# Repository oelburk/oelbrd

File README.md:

<!-- PROJECT SHIELDS -->
[![Contributors][contributors-shield]][contributors-url]
[![Forks][forks-shield]][forks-url]
[![Stargazers][stars-shield]][stars-url]
[![Issues][issues-shield]][issues-url]
[![MIT License][license-shield]][license-url]

<!-- PROJECT LOGO -->
<br />
<div align="center">

<h3 align="center">OELBRD</h3>

  <p align="center">
    Custom designed keyboard PCB and Firmware
    <br />
    <a href="https://github.com/oelburk/oelbrd/issues">Report Bug</a>
    ·
    <a href="https://github.com/oelburk/oelbrd/issues">Request Feature</a>
  </p>
</div>

<!-- TABLE OF CONTENTS -->
<details>
  <summary>Table of Contents</summary>
  <ol>
    <li>
      <a href="#about-the-project">About The Project</a>
      <ul>
        <li><a href="#built-with">Built With</a></li>
      </ul>
    </li>
    <li>
      <a href="#getting-started">Getting Started (Keymap setup)</a>
      <ul>
        <li><a href="#prerequisites">Prerequisites</a></li>
        <li><a href="#installation">Creating a keymap</a></li>
      </ul>
    </li>
    <li><a href="#contributing">Contributing</a></li>
    <li><a href="#license">License</a></li>
    <li><a href="#acknowledgments">Acknowledgments</a></li>
  </ol>
</details>

<!-- ABOUT THE PROJECT -->
## About The Project

![Product Name Screen Shot][product-screenshot]

Small project containing the PCB design files (KiCad project) along with the source code for different keymaps for my custom designed 60% keyboard.

<p align="right">(<a href="#readme-top">back to top</a>)</p>

### Built With

* [KiCad](https://www.kicad.org/download/windows/)
  * https://github.com/egladman/keebs.pretty
  * https://github.com/tmk/keyboard_parts.pretty
* [QMK](https://qmk.fm/)

<p align="right">(<a href="#readme-top">back to top</a>)</p>

<!-- GETTING STARTED -->
## Getting Started (Keymap setup)

This is an example of how you can create your own keymap for the oelbrd.

### Prerequisites
* Text editor of choice
* [QMK](https://github.com/qmk/qmk_firmware/blob/master/docs/newbs.md)

### Creating a keymap

1. Clone the repo
   ```sh
   git clone https://github.com/oelburk/oelbrd.git
   ```
2. Create new folder in keymaps folder
   ```sh
   mkdir QMK/keymaps/my-keymap
   ```
3. Copy default keymap (optional)
   ```sh
   cp QMK/keymaps/default/keymap.c QMK/keymaps/my-keymap
   ```
4. Edit `keymap.c` with preferred layout
5. Create oelbrd in QMK
   ```sh
   qmk new-keyboard oelbrd
   ```
6. Copy over contents from the QMK folder to new oelbrd directory in QMK repo, usally `../qmk_firmware/keyboards/oelbrd`
7. Compile the new keymap using QMK
   ```sh
   qmk compile -kb oelbrd -kb my-keymap
   ```
8. Flash new layout

### VIA support

There are currently some strange issues with the implemented VIA support, complaining about missing version definitons etc.

To fix this issue:
1. Open `qmk_firware/quantum/via.h`
2. Replace the define `VIA_PROTOCOL_VERSION` at row 62
   ```C
    VIA_PROTOCOL_VERSION 0x0009
   ```
3. Re-compile your keymap.
4. Enjoy VIA!

<p align="right">(<a href="#readme-top">back to top</a>)</p>

<!-- CONTRIBUTING -->
## Contributing

Contributions are what make the open source community such an amazing place to learn, inspire, and create. Any contributions you make are **greatly appreciated**.

If you have a suggestion that would make this better, please fork the repo and create a pull request. You can also simply open an issue with the tag "enhancement".
Don't forget to give the project a star! Thanks again!

1. Fork the Project
2. Create your Feature Branch (`git checkout -b feature/AmazingFeature`)
3. Commit your Changes (`git commit -m 'Add some AmazingFeature'`)
4. Push to the Branch (`git push origin feature/AmazingFeature`)
5. Open a Pull Request

<p align="right">(<a href="#readme-top">back to top</a>)</p>

<!-- LICENSE -->
## License

Distributed under the MIT License. See `LICENSE.txt` for more information.

<p align="right">(<a href="#readme-top">back to top</a>)</p>

<!-- ACKNOWLEDGMENTS -->
## Acknowledgments

* [Shoutout othneildrew for nice README template](https://github.com/othneildrew/Best-README-Template)
* [Swe Mech Keebs Community](http://mekaniskatangentbord.se/)

<p align="right">(<a href="#readme-top">back to top</a>)</p>

<!-- MARKDOWN LINKS & IMAGES -->
<!-- https://www.markdownguide.org/basic-syntax/#reference-style-links -->
[contributors-shield]: https://img.shields.io/github/contributors/oelburk/oelbrd.svg?style=for-the-badge
[contributors-url]: https://github.com/oelburk/oelbrd/graphs/contributors
[forks-shield]: https://img.shields.io/github/forks/oelburk/oelbrd.svg?style=for-the-badge
[forks-url]: https://github.com/oelburk/oelbrd/network/members
[stars-shield]: https://img.shields.io/github/stars/oelburk/oelbrd.svg?style=for-the-badge
[stars-url]: https://github.com/oelburk/oelbrd/stargazers
[issues-shield]: https://img.shields.io/github/issues/oelburk/oelbrd.svg?style=for-the-badge
[issues-url]: https://github.com/oelburk/oelbrd/issues
[license-shield]: https://img.shields.io/github/license/oelburk/oelbrd.svg?style=for-the-badge
[license-url]: https://github.com/oelburk/oelbrd/blob/master/LICENSE.txt
[linkedin-shield]: https://img.shields.io/badge/-LinkedIn-black.svg?style=for-the-badge&logo=linkedin&colorB=555
[linkedin-url]: https://linkedin.com/in/linkedin_username
[product-screenshot]: Design/oelbrd-mk1.jpg
[Next.js]: https://img.shields.io/badge/next.js-000000?style=for-the-badge&logo=nextdotjs&logoColor=white
[Next-url]: https://nextjs.org/
[React.js]: https://img.shields.io/badge/React-20232A?style=for-the-badge&logo=react&logoColor=61DAFB
[React-url]: https://reactjs.org/
[Vue.js]: https://img.shields.io/badge/Vue.js-35495E?style=for-the-badge&logo=vuedotjs&logoColor=4FC08D
[Vue-url]: https://vuejs.org/
[Angular.io]: https://img.shields.io/badge/Angular-DD0031?style=for-the-badge&logo=angular&logoColor=white
[Angular-url]: https://angular.io/
[Svelte.dev]: https://img.shields.io/badge/Svelte-4A4A55?style=for-the-badge&logo=svelte&logoColor=FF3E00
[Svelte-url]: https://svelte.dev/
[Laravel.com]: https://img.shields.io/badge/Laravel-FF2D20?style=for-the-badge&logo=laravel&logoColor=white
[Laravel-url]: https://laravel.com
[Bootstrap.com]: https://img.shields.io/badge/Bootstrap-563D7C?style=for-the-badge&logo=bootstrap&logoColor=white
[Bootstrap-url]: https://getbootstrap.com
[JQuery.com]: https://img.shields.io/badge/jQuery-0769AD?style=for-the-badge&logo=jquery&logoColor=white
[JQuery-url]: https://jquery.com

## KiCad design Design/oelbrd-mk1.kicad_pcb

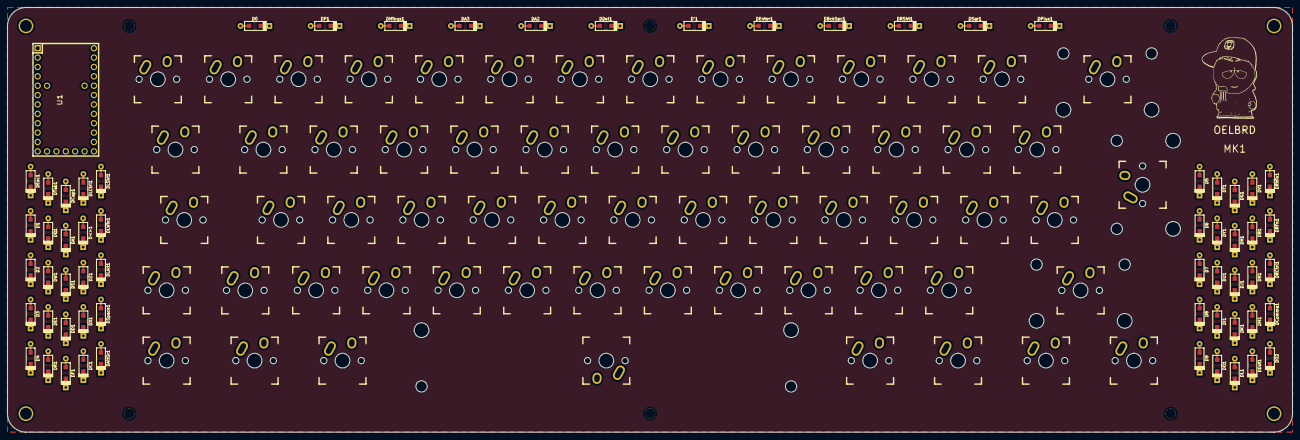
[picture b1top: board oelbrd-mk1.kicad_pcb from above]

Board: 2 copper layers, 348.0 x 115.0 mm, 135 parts (0 on the bottom side), 82 nets, no tracks yet.

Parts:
D0, D1, D2, D3, D4, D5, D6, D7, D8, D9: D; D_SOD123_axial
D'1: D; D_SOD123_axial
D<>1: D; D_SOD123_axial
DA1, DA2, DA3: D; D_SOD123_axial
DAltGr1: D; D_SOD123_axial
DB1: D; D_SOD123_axial
DBckSpc1: D; D_SOD123_axial
DC1: D; D_SOD123_axial
DCap1: D; D_SOD123_axial
DComma1: D; D_SOD123_axial
DD1: D; D_SOD123_axial
DDel1: D; D_SOD123_axial
DDot1: D; D_SOD123_axial
DE1: D; D_SOD123_axial
DEnter1: D; D_SOD123_axial
DEsc1: D; D_SOD123_axial
DF1: D; D_SOD123_axial
DG1: D; D_SOD123_axial
DH1: D; D_SOD123_axial
DI1: D; D_SOD123_axial
DJ1: D; D_SOD123_axial
DK1: D; D_SOD123_axial
DL1: D; D_SOD123_axial
DLAlt1: D; D_SOD123_axial
DLCtrl1: D; D_SOD123_axial
DLSht1: D; D_SOD123_axial
DLWin1: D; D_SOD123_axial
DM1: D; D_SOD123_axial
DMinus1: D; D_SOD123_axial
DN1: D; D_SOD123_axial
DO1, DO2: D; D_SOD123_axial
DP1: D; D_SOD123_axial
DPlus1: D; D_SOD123_axial
DQ1: D; D_SOD123_axial
DR1: D; D_SOD123_axial
DRCtrl1: D; D_SOD123_axial
DRFn1: D; D_SOD123_axial
DRSht1: D; D_SOD123_axial
DRWin1: D; D_SOD123_axial
DS1: D; D_SOD123_axial
DSpace1: D; D_SOD123_axial
DSqr1: D; D_SOD123_axial
DT1: D; D_SOD123_axial
DTab1: D; D_SOD123_axial
DU1: D; D_SOD123_axial
DV1: D; D_SOD123_axial
DW1: D; D_SOD123_axial
DX1: D; D_SOD123_axial
DY1: D; D_SOD123_axial
DZ1: D; D_SOD123_axial
HOLE_M2.6, HOLE_M2.6#2, HOLE_M2.6#3, HOLE_M2.6#4, HOLE_M2.6#5, HOLE_M2.6#6: VAL**; HOLE_M2.6
HOLE_M3, HOLE_M3#2, HOLE_M3#3, HOLE_M3#4: VAL**; HOLE_M3
K0, K1, K2, K3, K4, K5, K6, K7, K8, K9: KEYSW; Mx_Alps_100
K'1: KEYSW; Mx_Alps_100
K<>1: KEYSW; Mx_Alps_100
KA1, KA2, KA3: KEYSW; Mx_Alps_100
KAltGr1: KEYSW; Mx_Alps_125
KB1: KEYSW; Mx_Alps_100
KBckSpc1: KEYSW; Mx_Alps_200
KC1: KEYSW; Mx_Alps_100
KCap1: KEYSW; Mx_Alps_175
KComma1: KEYSW; Mx_Alps_100
KD1: KEYSW; Mx_Alps_100
KDel1: KEYSW; Mx_Alps_100
KDot1: KEYSW; Mx_Alps_100
KE1: KEYSW; Mx_Alps_100
KEnter1: KEYSW; Mx_Alps_200
KEsc1: KEYSW; Mx_Alps_100
KF1: KEYSW; Mx_Alps_100
KG1: KEYSW; Mx_Alps_100
KH1: KEYSW; Mx_Alps_100
KI1: KEYSW; Mx_Alps_100
KJ1: KEYSW; Mx_Alps_100
KK1: KEYSW; Mx_Alps_100
KL1: KEYSW; Mx_Alps_100
KLAlt1: KEYSW; Mx_Alps_125
KLCtrl1: KEYSW; Mx_Alps_125
KLSht1: KEYSW; Mx_Alps_125
KLWin1: KEYSW; Mx_Alps_125
KM1: KEYSW; Mx_Alps_100
KMinus1: KEYSW; Mx_Alps_100
KN1: KEYSW; Mx_Alps_100
KO1, KO2: KEYSW; Mx_Alps_100
KP1: KEYSW; Mx_Alps_100
KPlus1: KEYSW; Mx_Alps_100
KQ1: KEYSW; Mx_Alps_100
KR1: KEYSW; Mx_Alps_100
KRCtrl1: KEYSW; Mx_Alps_125
KRFn1: KEYSW; Mx_Alps_125
KRSht1: KEYSW; Mx_Alps_275
KRWin1: KEYSW; Mx_Alps_125
KS1: KEYSW; Mx_Alps_100
KSpace1: KEYSW; Mx_Alps_625
KSqr1: KEYSW; Mx_Alps_100
KT1: KEYSW; Mx_Alps_100
KTab1: KEYSW; Mx_Alps_150
KU1: KEYSW; Mx_Alps_100
KV1: KEYSW; Mx_Alps_100
KW1: KEYSW; Mx_Alps_100
KX1: KEYSW; Mx_Alps_100
KY1: KEYSW; Mx_Alps_100
KZ1: KEYSW; Mx_Alps_100
U1: TEENSY2.0; Teensy_20

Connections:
/col0: KCap1.1, KEsc1.1, KLCtrl1.1, KLSht1.1, KTab1.1, U1.21
/col1: K1.1, K<>1.1, KA1.1, KLWin1.1, KQ1.1, U1.22
/col2: K2.1, KLAlt1.1, KS1.1, KW1.1, KZ1.1, U1.6
/col3: K3.1, KD1.1, KE1.1, KSpace1.1, KX1.1, U1.11
/col4: K4.1, KAltGr1.1, KC1.1, KF1.1, KR1.1, U1.12
/col5: K5.1, KG1.1, KRWin1.1, KT1.1, KV1.1, U1.7
/col6: K6.1, KB1.1, KH1.1, KRFn1.1, KY1.1, U1.8
/col7: K7.1, KJ1.1, KN1.1, KRCtrl1.1, KU1.1, U1.9
/col8: K8.1, KI1.1, KK1.1, KM1.1, U1.10
/col9: K9.1, KComma1.1, KL1.1, KO1.1, U1.17
/col10: K0.1, KDot1.1, KO2.1, KP1.1, U1.13
/col11: KA2.1, KA3.1, KMinus1.1, KPlus1.1, U1.19
/col12: K'1.1, KDel1.1, KRSht1.1, KSqr1.1, U1.31
/col13: KBckSpc1.1, KEnter1.1, U1.28
/row0: D0.1, D1.1, D2.1, D3.1, D4.1, D5.1, D6.1, D7.1, D8.1, D9.1, DBckSpc1.1, DDel1.1, DEsc1.1, DPlus1.1, U1.2
/row1: DA2.1, DE1.1, DEnter1.1, DI1.1, DO1.1, DP1.1, DQ1.1, DR1.1, DSqr1.1, DT1.1, DTab1.1, DU1.1, DW1.1, DY1.1, U1.3
/row2: D'1.1, DA1.1, DA3.1, DCap1.1, DD1.1, DF1.1, DG1.1, DH1.1, DJ1.1, DK1.1, DL1.1, DO2.1, DS1.1, U1.4
/row3: D<>1.1, DB1.1, DC1.1, DComma1.1, DDot1.1, DLSht1.1, DM1.1, DMinus1.1, DN1.1, DRSht1.1, DV1.1, DX1.1, DZ1.1, U1.5
/row4: DAltGr1.1, DLAlt1.1, DLCtrl1.1, DLWin1.1, DRCtrl1.1, DRFn1.1, DRWin1.1, DSpace1.1, U1.20
GND: U1.1, U1.15
unnamed: D0.2, K0.2
unnamed: D1.2, K1.2
unnamed: D2.2, K2.2
unnamed: D3.2, K3.2
unnamed: D4.2, K4.2
unnamed: D5.2, K5.2
unnamed: D6.2, K6.2
unnamed: D7.2, K7.2
unnamed: D8.2, K8.2
unnamed: D9.2, K9.2
unnamed: D'1.2, K'1.2
unnamed: D<>1.2, K<>1.2
unnamed: DA1.2, KA1.2
unnamed: DA2.2, KA2.2
unnamed: DA3.2, KA3.2
unnamed: DAltGr1.2, KAltGr1.2
unnamed: DB1.2, KB1.2
unnamed: DBckSpc1.2, KBckSpc1.2
unnamed: DC1.2, KC1.2
unnamed: DCap1.2, KCap1.2
unnamed: DComma1.2, KComma1.2
unnamed: DD1.2, KD1.2
unnamed: DDel1.2, KDel1.2
unnamed: DDot1.2, KDot1.2
unnamed: DE1.2, KE1.2
unnamed: DEnter1.2, KEnter1.2
unnamed: DEsc1.2, KEsc1.2
unnamed: DF1.2, KF1.2
unnamed: DG1.2, KG1.2
unnamed: DH1.2, KH1.2
unnamed: DI1.2, KI1.2
unnamed: DJ1.2, KJ1.2
unnamed: DK1.2, KK1.2
unnamed: DL1.2, KL1.2
unnamed: DLAlt1.2, KLAlt1.2
unnamed: DLCtrl1.2, KLCtrl1.2
unnamed: DLSht1.2, KLSht1.2
unnamed: DLWin1.2, KLWin1.2
unnamed: DM1.2, KM1.2
unnamed: DMinus1.2, KMinus1.2
unnamed: DN1.2, KN1.2
unnamed: DO1.2, KO1.2
unnamed: DO2.2, KO2.2
unnamed: DP1.2, KP1.2
unnamed: DPlus1.2, KPlus1.2
unnamed: DQ1.2, KQ1.2
unnamed: DR1.2, KR1.2
unnamed: DRCtrl1.2, KRCtrl1.2
unnamed: DRFn1.2, KRFn1.2
unnamed: DRSht1.2, KRSht1.2
unnamed: DRWin1.2, KRWin1.2
unnamed: DS1.2, KS1.2
unnamed: DSpace1.2, KSpace1.2
unnamed: DSqr1.2, KSqr1.2
unnamed: DT1.2, KT1.2
unnamed: DTab1.2, KTab1.2
unnamed: DU1.2, KU1.2
unnamed: DV1.2, KV1.2
unnamed: DW1.2, KW1.2
unnamed: DX1.2, KX1.2
unnamed: DY1.2, KY1.2
unnamed: DZ1.2, KZ1.2

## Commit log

2023-09-23 Initial add
2023-09-23 update default keymap
2023-09-23 Partial VIA support
2023-09-23 Add new keymap, info about VIA
2023-09-23 add detailed instructions
2023-09-23 fix QMK readme
2023-09-23 remove img link
